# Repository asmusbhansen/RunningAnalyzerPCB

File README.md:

# RunningAnalyzerPCB
Custom PCB for the RunningAnalyzer data logger

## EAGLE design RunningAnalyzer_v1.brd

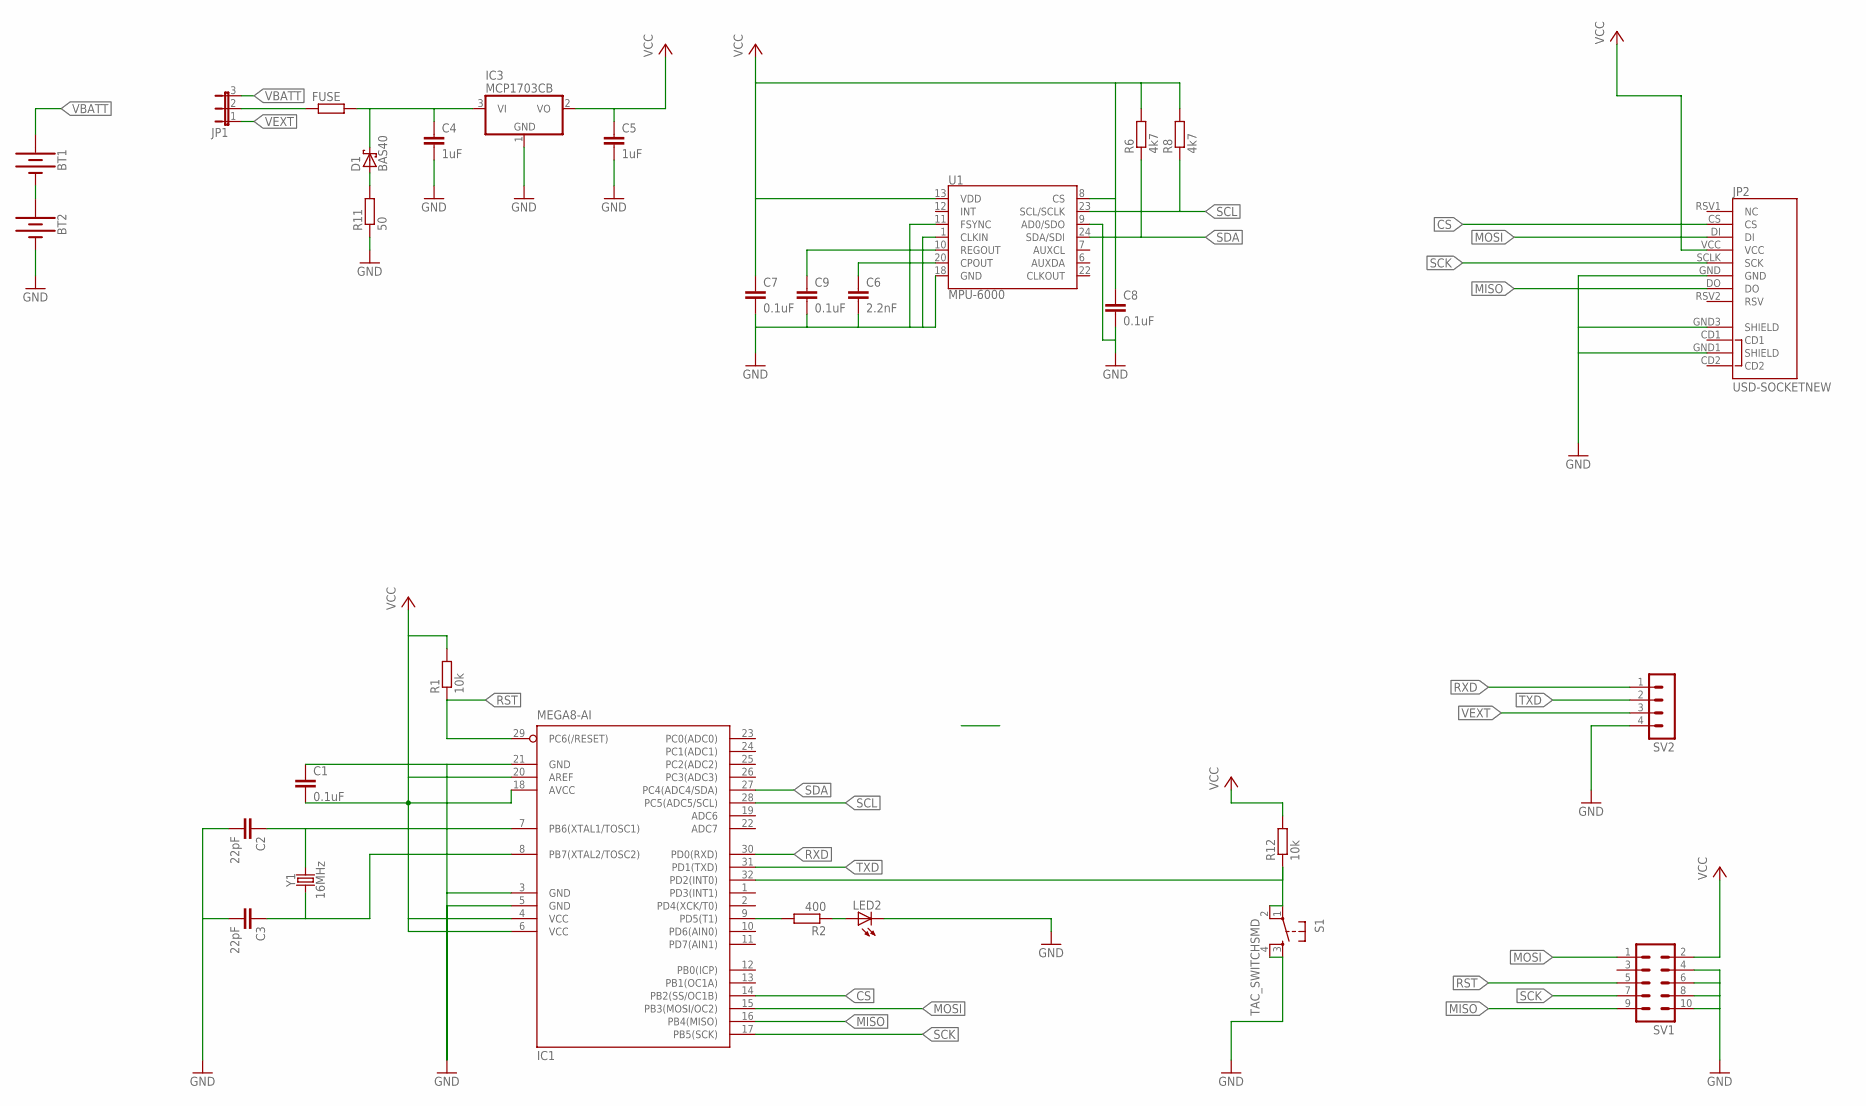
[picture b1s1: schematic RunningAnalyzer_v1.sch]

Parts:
BT1, BT2: BATTERY-20MM_SMD_4LEGS_OVERPASTE; BATTCON_20MM_4LEGS_OVERPASTE
C1, C7, C8, C9: 0.1uF; C0805
C2, C3: 22pF; C0805
C4, C5: 1uF; C0805
C6: 2.2nF; C0805
D1: BAS40; SOT23
FUSE: R-EU_M1206; M1206
IC1: MEGA8-AI; TQFP32-08
IC3: MCP1703CB; SOT23
JP1: JP2E; JP2
JP2: USD-SOCKETNEW; MICRO-SD-SOCKET-PP
LED2: LED_E; LED_1206
R1, R12: 10k; R1206
R2: 400; R0805
R6, R8: 4k7; R0805
R11: 50; R0805
S1: TAC_SWITCHSMD; TACTILE-SWITCH-SMD
SV1: MA05-2
SV2: MA04-1
U1: MPU-6000; QFN-24-EP
Y1: 16MHz; HC49UP

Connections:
CS: IC1.14 (PB2(SS/OC1B)), JP2.CS
GND: BT2.2 (-), C1.1, C2.2, C3.2, C4.2, C5.2, C6.2, C7.2, C8.2, C9.2, IC1.3 (GND), IC1.5 (GND), IC1.21 (GND), IC3.1 (GND), JP2.GND, JP2.GND1 (SHIELD), JP2.GND3 (SHIELD), LED2.C, R11.1, S1.3, S1.4, SV1.4, SV1.6, SV1.8, SV1.10, SV2.4, U1.1 (CLKIN), U1.9 (AD0/SDO), U1.11 (FSYNC), U1.18 (GND)
MISO: IC1.16 (PB4(MISO)), JP2.DO, SV1.9
MOSI: IC1.15 (PB3(MOSI/OC2)), JP2.DI, SV1.1
unnamed: IC1.9 (PD5(T1)), R2.2
unnamed: C6.1, U1.20 (CPOUT)
unnamed: C9.1, U1.10 (REGOUT)
unnamed: D1.1 (A), R11.2
unnamed: C3.1, IC1.8 (PB7(XTAL2/TOSC2)), Y1.1
unnamed: C2.1, IC1.7 (PB6(XTAL1/TOSC1)), Y1.2
unnamed: IC1.32 (PD2(INT0)), R12.1, S1.1, S1.2
unnamed: LED2.A, R2.1
unnamed: FUSE.1, JP1.2
unnamed: BT1.2 (-), BT2.1 (+)
unnamed: C4.1, D1.3 (C), FUSE.2, IC3.3 (VI)
RST: IC1.29 (PC6(/RESET)), R1.1, SV1.5
RXD: IC1.30 (PD0(RXD)), SV2.1
SCK: IC1.17 (PB5(SCK)), JP2.SCLK (SCK), SV1.7
SCL: IC1.28 (PC5(ADC5/SCL)), R8.1, U1.23 (SCL/SCLK)
SDA: IC1.27 (PC4(ADC4/SDA)), R6.1, U1.24 (SDA/SDI)
TXD: IC1.31 (PD1(TXD)), SV2.2
VBATT: BT1.1 (+), JP1.3
VCC: C1.2, C5.1, C7.1, C8.1, IC1.4 (VCC), IC1.6 (VCC), IC1.18 (AVCC), IC1.20 (AREF), IC3.2 (VO), JP2.VCC, R1.2, R6.2, R8.2, R12.2, SV1.2, U1.8 (CS), U1.13 (VDD)
VEXT: JP1.1, SV2.3

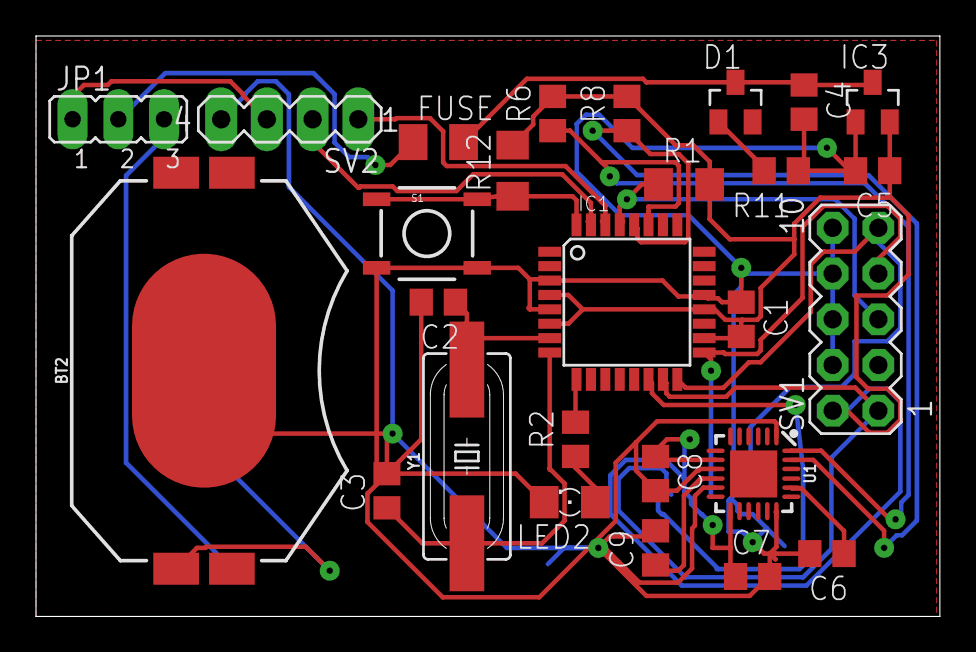
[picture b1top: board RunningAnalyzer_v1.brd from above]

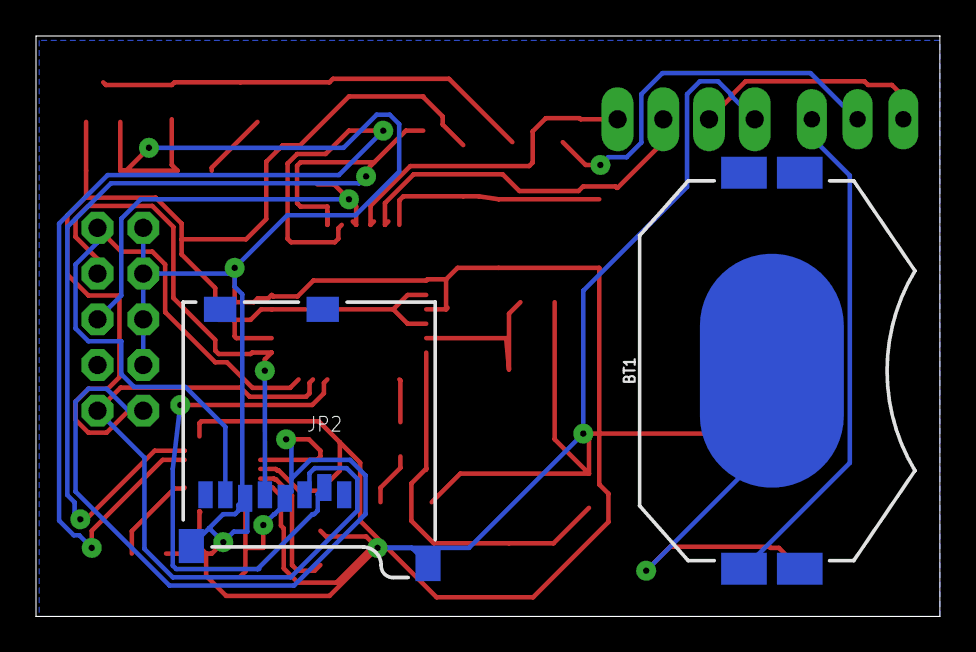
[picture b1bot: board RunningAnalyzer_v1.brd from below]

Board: 2 copper layers, 50.2 x 32.2 mm, 29 parts (2 on the bottom side), 24 nets.

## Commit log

2018-06-16 RunningAnalyzer PCB first commit

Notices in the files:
parts and their libraries:
SparkFun-Batteries: Licensing: Creative Commons ShareAlike 4.0 International - https://creativecommons.org/licenses/by-sa/4.0
